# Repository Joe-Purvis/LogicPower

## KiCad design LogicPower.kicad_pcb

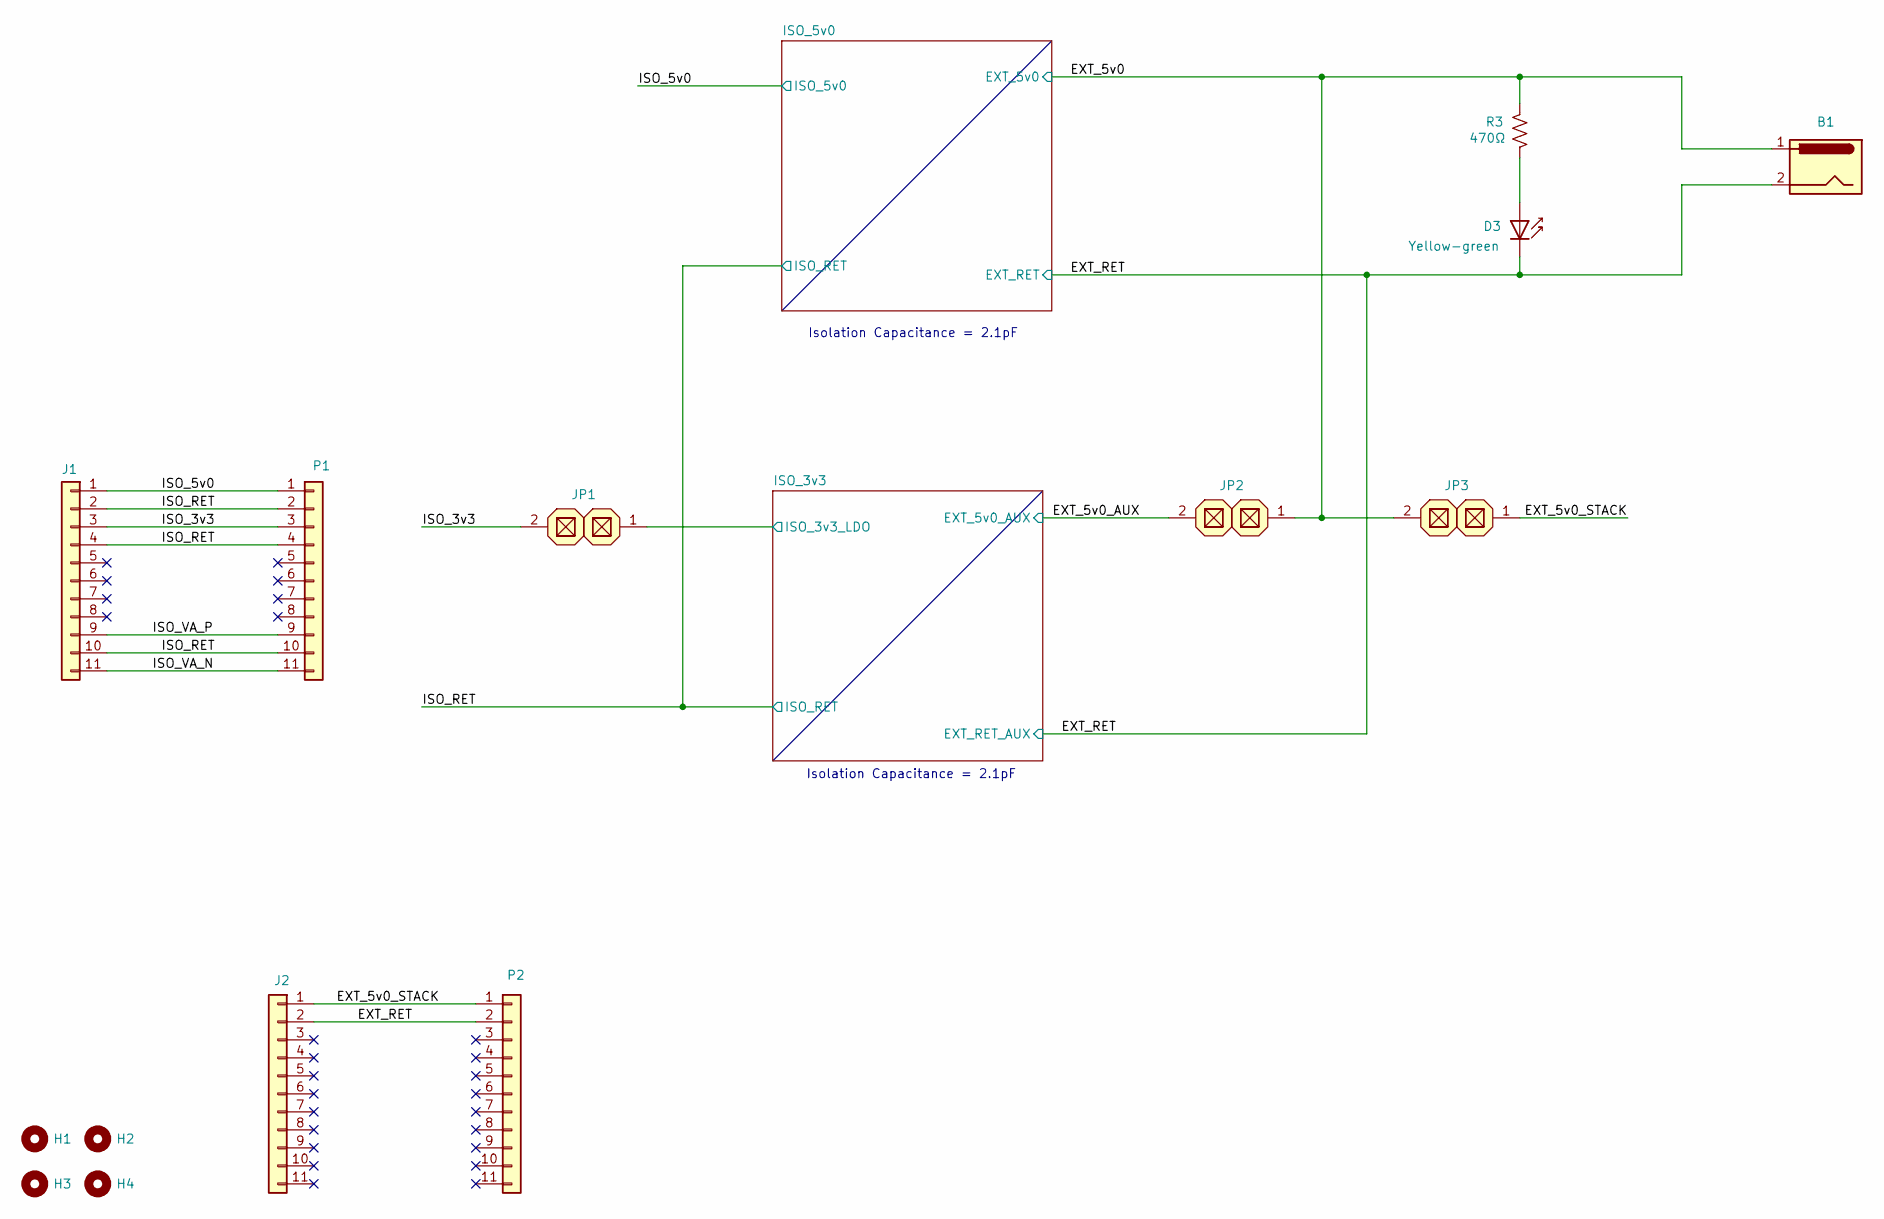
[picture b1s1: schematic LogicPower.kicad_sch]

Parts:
B1: Barrel_Jack; BarrelJack_CUI_PJ-063AH_Horizontal
D3: Yellow-green; LED_1206_3216Metric; LCSC C6491384
H1, H2, H3, H4: MountingHole; MountingHole_2.2mm_M2
J1, J2: Conn_01x11; PinSocket_1x11_P2.54mm_Vertical
JP1, JP2, JP3: Conn_01x02; PinHeader_1x02_P2.54mm_Vertical
P1, P2: Conn_01x11; PinHeader_1x11_P2.54mm_Vertical
R3: 470Ω; R_1206_3216Metric_Pad1.30x1.75mm_HandSolder; LCSC C25383

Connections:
/EXT_5v0: B1.1, JP2.1, JP3.2, R3.2; also elsewhere on the board
/EXT_5v0_AUX: JP2.2; also elsewhere on the board
/EXT_5v0_STACK: J2.1, JP3.1, P2.1
/EXT_RET: B1.2, D3.1 (K), J2.2, P2.2; also elsewhere on the board
/ISO_3v3: J1.3, JP1.2, P1.3
/ISO_3v3/ISO_3v3_LDO: JP1.1; also elsewhere on the board
/ISO_5v0: J1.1, P1.1; also elsewhere on the board
/ISO_RET: J1.2, J1.4, J1.10, P1.2, P1.4, P1.10; also elsewhere on the board
/ISO_VA_N: J1.11, P1.11
/ISO_VA_P: J1.9, P1.9
unnamed: D3.2 (A), R3.1

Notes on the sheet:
Isolation Capacitance = 2.1pF

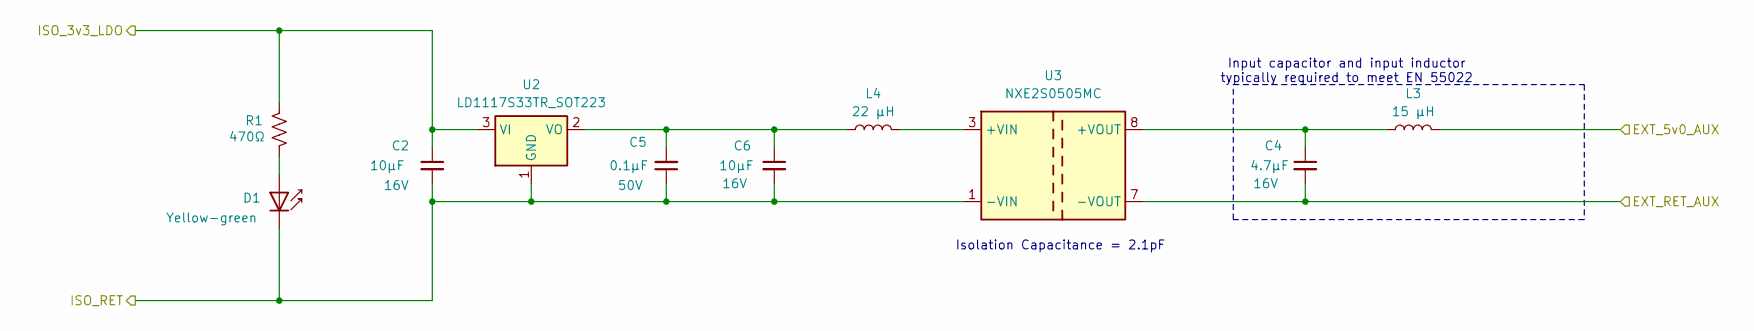
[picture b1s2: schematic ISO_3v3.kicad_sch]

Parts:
C2, C6: 10µF; C_1210_3225Metric_Pad1.33x2.70mm_HandSolder; Voltage Rating 16V; LCSC C307584
C4: 4.7µF; C_1206_3216Metric; Voltage Rating 16V; LCSC C237223
C5: 0.1µF; C_1206_3216Metric_Pad1.33x1.80mm_HandSolder; Voltage Rating 50V; LCSC C24497
D1: Yellow-green; LED_1206_3216Metric; LCSC C6491384
L3: 15 µH; L_Changjiang_FNR4018S; LCSC C167809
L4: 22 µH; IND_8400_84XXXC_MUR; LCSC C341013
R1: 470Ω; R_1206_3216Metric_Pad1.30x1.75mm_HandSolder; LCSC C25383
U2: LD1117S33TR_SOT223; SOT-223-3_TabPin2; LCSC C86781
U3: NXE2S0505MC; Converter_DCDC_Murata_NXExSxxxxMC_SMD; LCSC C5817088

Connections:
/EXT_5v0_AUX: L3.2; also elsewhere on the board
/EXT_RET: C4.2, U3.7 (-VOUT); also elsewhere on the board
/ISO_3v3/ISO_3v3_LDO: C2.1, R1.2, U2.3 (VI); also elsewhere on the board
/ISO_RET: C2.2, C5.1, C6.2, D1.1 (K), U2.1 (GND), U3.1 (-VIN); also elsewhere on the board
unnamed: D1.2 (A), R1.1
unnamed: C5.2, C6.1, L4.1, U2.2 (VO)
unnamed: L4.2, U3.3 (+VIN)
unnamed: C4.1, L3.1, U3.8 (+VOUT)

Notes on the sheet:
Input capacitor and input inductor typically required to meet EN 55022
Isolation Capacitance = 2.1pF

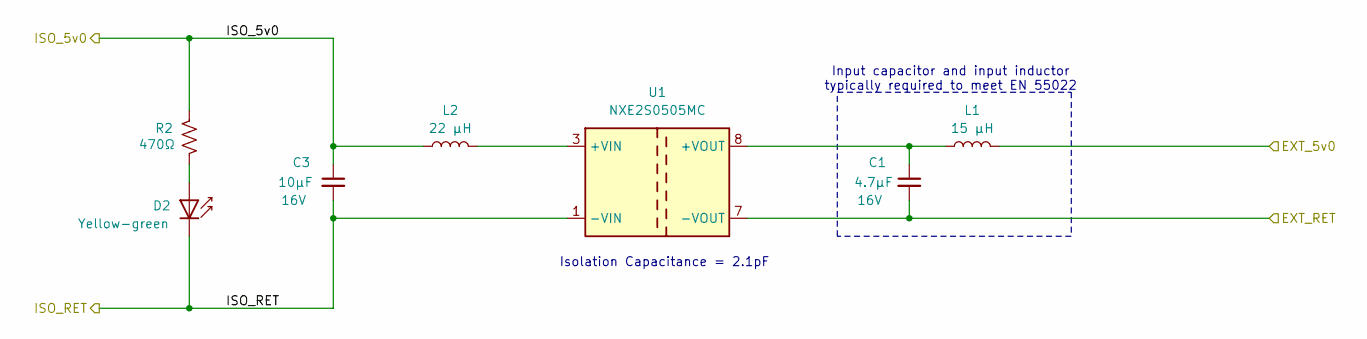
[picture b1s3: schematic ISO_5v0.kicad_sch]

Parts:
C1: 4.7µF; C_1206_3216Metric; Voltage Rating 16V; LCSC C237223
C3: 10µF; C_1210_3225Metric_Pad1.33x2.70mm_HandSolder; Voltage Rating 16V; LCSC C307584
D2: Yellow-green; LED_1206_3216Metric; LCSC C6491384
L1: 15 µH; L_Changjiang_FNR4018S; LCSC C167809
L2: 22 µH; IND_8400_84XXXC_MUR; LCSC C341013
R2: 470Ω; R_1206_3216Metric_Pad1.30x1.75mm_HandSolder; LCSC C25383
U1: NXE2S0505MC; Converter_DCDC_Murata_NXExSxxxxMC_SMD; LCSC C5817088

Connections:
/EXT_5v0: L1.2; also elsewhere on the board
/EXT_RET: C1.2, U1.7 (-VOUT); also elsewhere on the board
/ISO_5v0: C3.1, L2.1, R2.2; also elsewhere on the board
/ISO_RET: C3.2, D2.1 (K), U1.1 (-VIN); also elsewhere on the board
unnamed: D2.2 (A), R2.1
unnamed: L2.2, U1.3 (+VIN)
unnamed: C1.1, L1.1, U1.8 (+VOUT)

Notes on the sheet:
Isolation Capacitance = 2.1pF
Input capacitor and input inductor typically required to meet EN 55022

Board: 2 copper layers, 31 parts (2 on the bottom side), 18 nets, no tracks yet.
